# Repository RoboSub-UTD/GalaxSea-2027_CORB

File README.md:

# galaxsea 2027 corb

wassup chat... i'm playing Grand Theft Auto VI......

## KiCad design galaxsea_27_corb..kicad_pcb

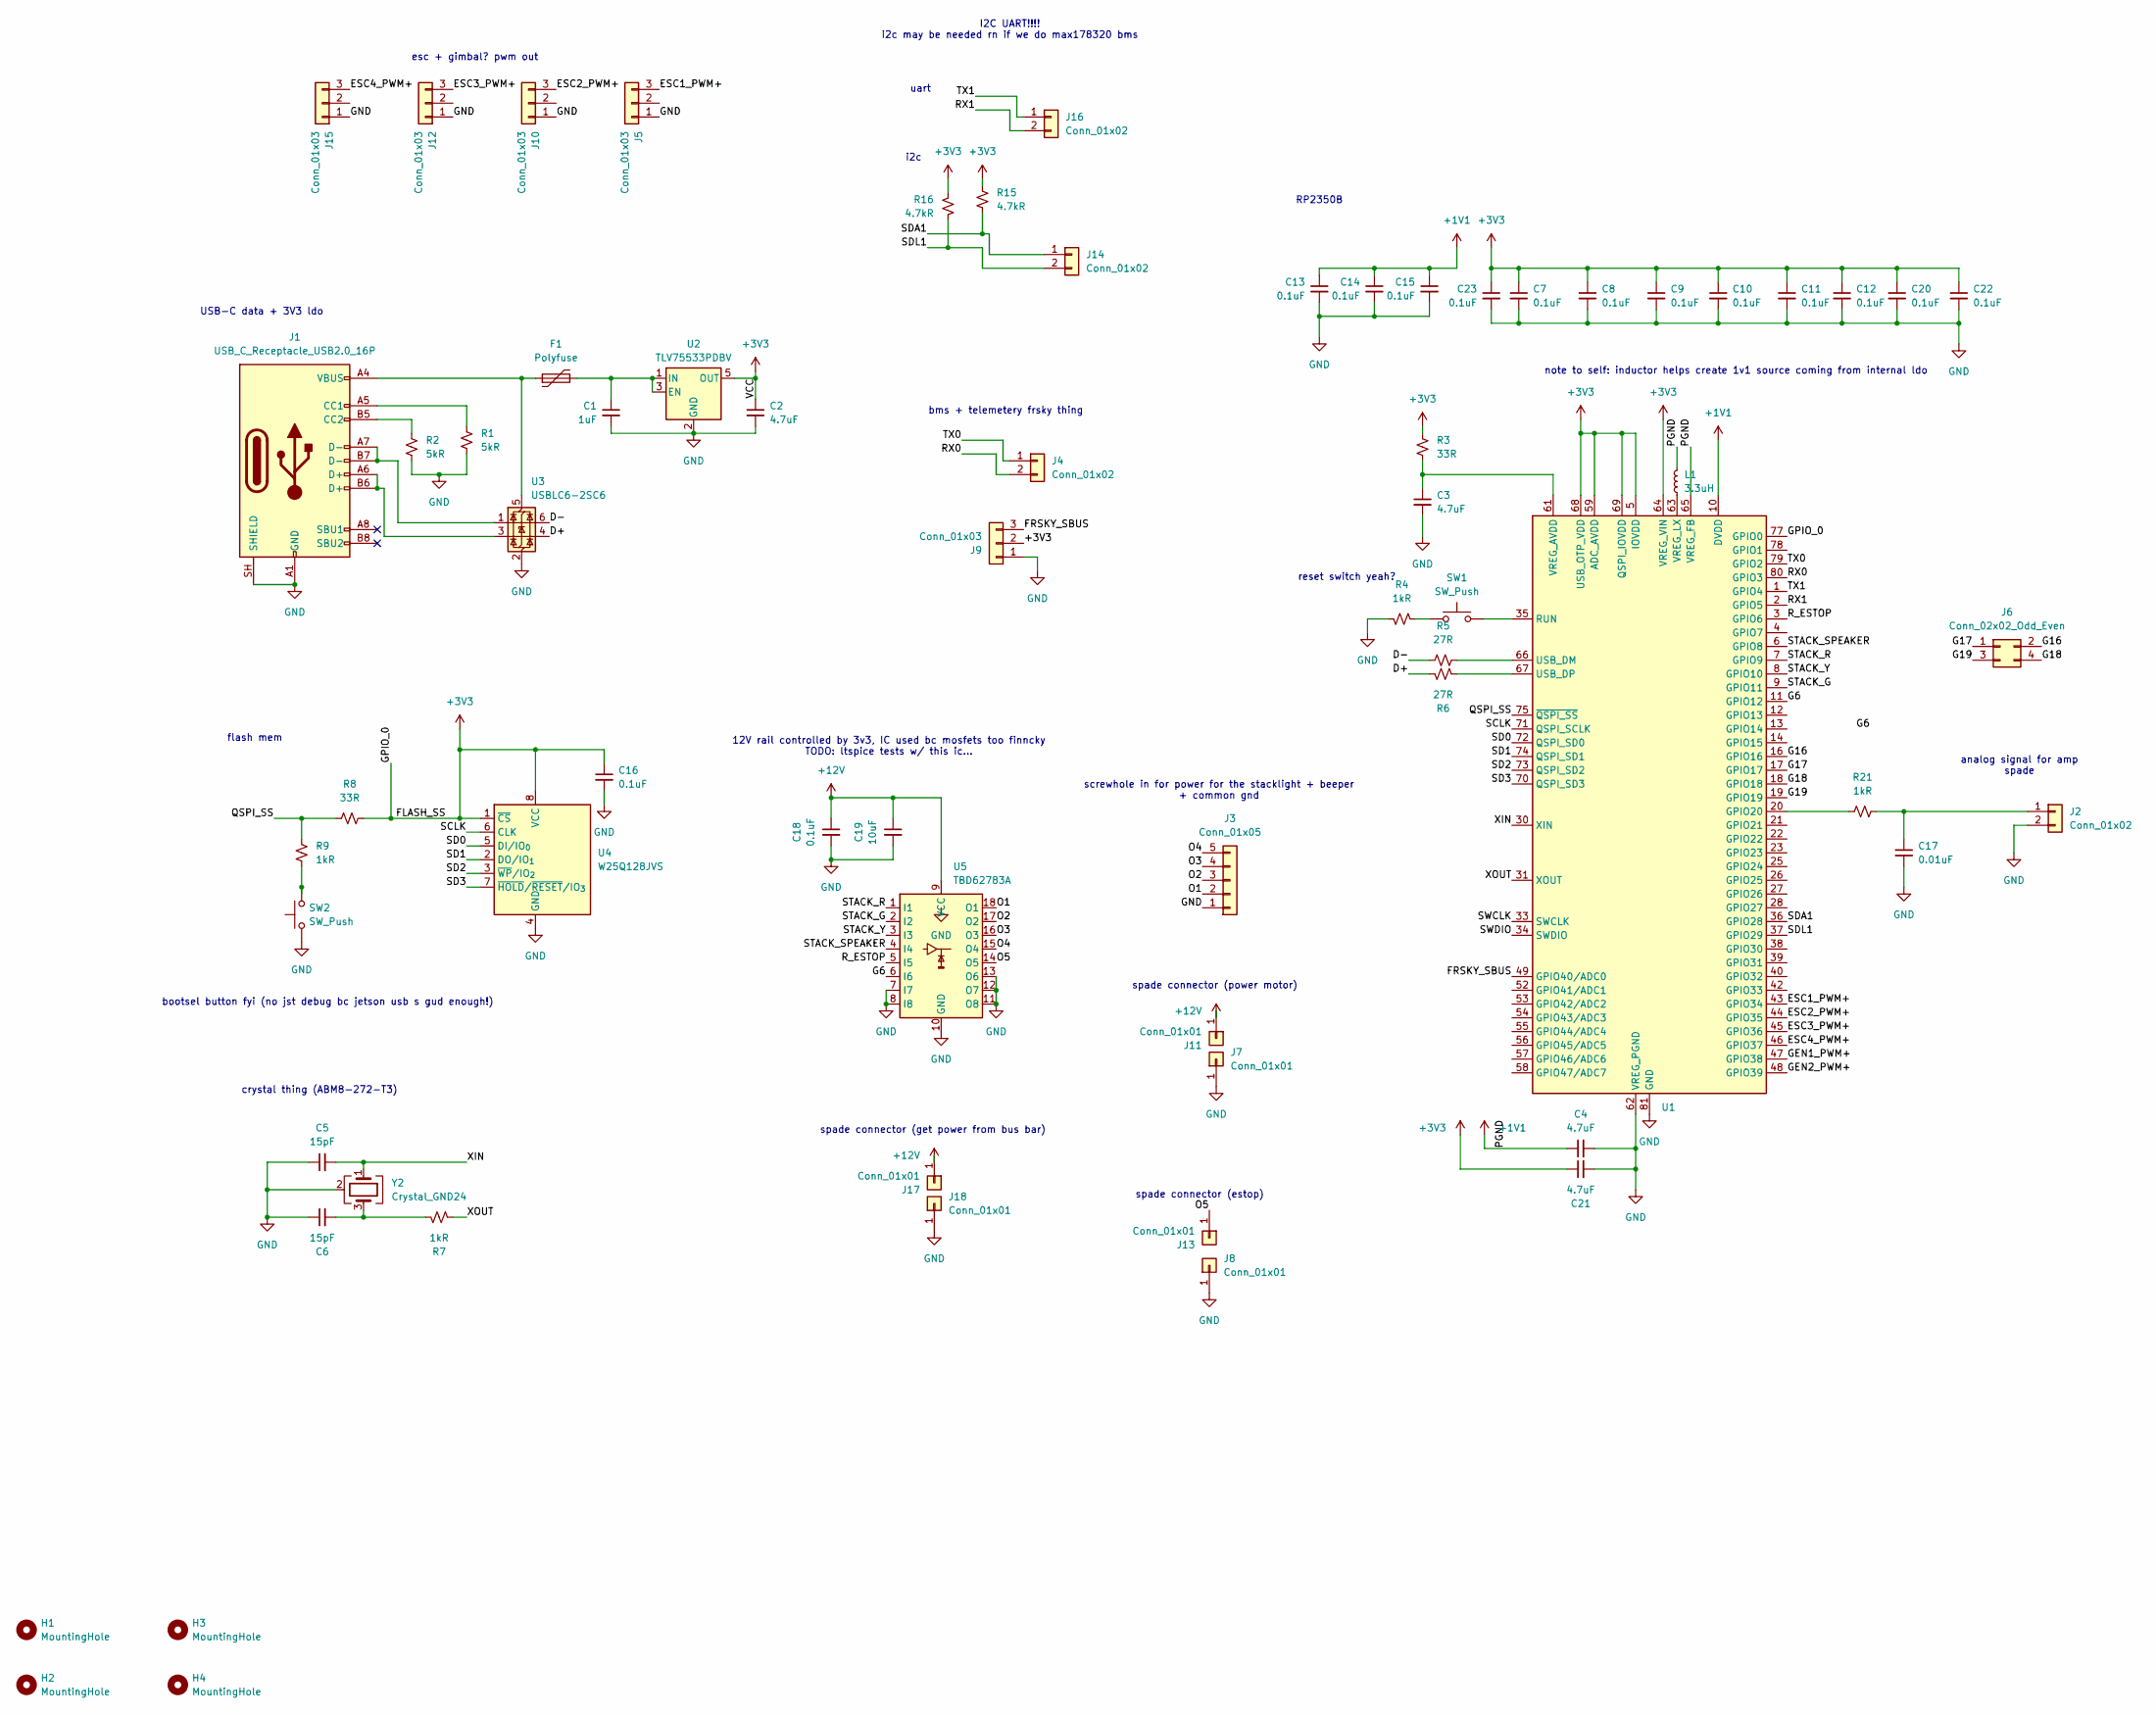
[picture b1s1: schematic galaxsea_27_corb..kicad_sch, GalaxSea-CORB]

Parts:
C1: 1uF; C_0603_1608Metric
C2, C3, C4, C21: 4.7uF; C_0603_1608Metric
C5, C6: 15pF; C_0603_1608Metric
C7, C8, C9, C10, C11, C12, C13, C14, C15, C16, C18, C20, C22, C23: 0.1uF; C_0603_1608Metric
C17: 0.01uF; C_0603_1608Metric
C19: 10uF; C_0603_1608Metric
F1: Polyfuse; Fuse_0603_1608Metric
H1, H2, H3, H4: MountingHole; MountingHole_3.2mm_M3
J1: USB_C_Receptacle_USB2.0_16P; USB_C_Receptacle_HRO_TYPE-C-31-M-12
J2, J4, J14, J16: Conn_01x02; JST_XH_B2B-XH-A_1x02_P2.50mm_Vertical
J3: Conn_01x05; TerminalBlock_RND_205-00015_1x05_P5.00mm_Horizontal
J5, J9, J10, J12, J15: Conn_01x03; JST_XH_B3B-XH-A_1x03_P2.50mm_Vertical
J6: Conn_02x02_Odd_Even; PinHeader_2x02_P2.54mm_Vertical
J7, J8, J11, J13, J17, J18: Conn_01x01; TestPoint_Bridge_Pitch5.08mm_Drill1.3mm
L1: 3.3uH; L_0603_1608Metric
R1, R2: 5kR; R_0603_1608Metric
R3, R8: 33R; R_0603_1608Metric
R4, R7, R9, R21: 1kR; R_0603_1608Metric
R5, R6: 27R; R_0603_1608Metric
R15, R16: 4.7kR; R_0603_1608Metric
SW1, SW2: SW_Push; SW_Push_1P1T_NO_Vertical_Wuerth_434133025816
U1: RP2350B; QFN-80-1EP_10x10mm_P0.4mm_EP3.4x3.4mm
U2: TLV75533PDBV; SOT-23-5
U3: USBLC6-2SC6; SOT-23-6
U4: W25Q128JVS; SOIC-8_5.3x5.3mm_P1.27mm
U5: TBD62783A; SOP-18_7x12.5mm_P1.27mm
Y2: Crystal_GND24; Crystal_SMD_3225-4Pin_3.2x2.5mm

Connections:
+1V1: C4.1, C13.1, C14.1, C15.1, L1.2, U1.10 (DVDD), U1.32 (DVDD), U1.51 (DVDD), U1.65 (VREG_FB)
+3V3: C2.1, C7.1, C8.1, C9.1, C10.1, C11.1, C12.1, C16.1, C20.1, C21.1, C22.1, C23.1, J9.2, R3.1, R8.2, R15.1, R16.1, U1.5 (IOVDD), U1.15 (IOVDD), U1.24 (IOVDD), U1.29 (IOVDD), U1.41 (IOVDD), U1.50 (IOVDD), U1.59 (ADC_AVDD), U1.60 (IOVDD), U1.64 (VREG_VIN), U1.68 (USB_OTP_VDD), U1.69 (QSPI_IOVDD), U1.76 (IOVDD), U1.77 (GPIO0), U2.5 (OUT), U4.1 (~CS), U4.8 (VCC)
+12V: C18.1, C19.1, J11.1 (Pin_1_1), J17.1 (Pin_1_1), U5.9 (VCC)
/A1: U1.52 (GPIO41/ADC1)
/A2: U1.53 (GPIO42/ADC2)
/A3: U1.54 (GPIO43/ADC3)
/A4: U1.55 (GPIO44/ADC4)
/A5: U1.56 (GPIO45/ADC5)
/A6: U1.57 (GPIO46/ADC6)
/A7: U1.58 (GPIO47/ADC7)
/D+: R6.2, U3.4 (I/O2)
/D-: R5.1, U3.6 (I/O1)
/ESC1_PWM+: J5.3, U1.43 (GPIO34)
/ESC2_PWM+: J10.3, U1.44 (GPIO35)
/ESC3_PWM+: J12.3, U1.45 (GPIO36)
/ESC4_PWM+: J15.3, U1.46 (GPIO37)
/FRSKY_SBUS: J9.3, U1.49 (GPIO40/ADC0)
/G6: U1.11 (GPIO12), U5.6 (I6)
/G16: J6.2, U1.16 (GPIO16)
/G17: J6.1, U1.17 (GPIO17)
/G18: J6.4, U1.18 (GPIO18)
/G19: J6.3, U1.19 (GPIO19)
/GEN1_PWM+: U1.47 (GPIO38)
/GEN2_PWM+: U1.48 (GPIO39)
/O1: J3.2, U5.18 (O1)
/O2: J3.3, U5.17 (O2)
/O3: J3.4, U5.16 (O3)
/O4: J3.5, U5.15 (O4)
/O5: J13.1 (Pin_1_1), U5.14 (O5)
/QSPI_SS: R8.1, R9.2, U1.75 (~QSPI_SS)
/RX0: J4.2, U1.80 (GPIO3)
/RX1: J16.2, U1.2 (GPIO5)
/R_ESTOP: U1.3 (GPIO6), U5.5 (I5)
/SCLK: U1.71 (QSPI_SCLK), U4.6 (CLK)
/SD0: U1.72 (QSPI_SD0), U4.5 (DI/IO_{0})
/SD1: U1.74 (QSPI_SD1), U4.2 (DO/IO_{1})
/SD2: U1.73 (QSPI_SD2), U4.3 (~WP/IO_{2})
/SD3: U1.70 (QSPI_SD3), U4.7 (~HOLD/~RESET/IO_{3})
/SDA1: J14.1, R15.2, U1.36 (GPIO28)
/SDL1: J14.2, R16.2, U1.37 (GPIO29)
/STACK_G: U1.9 (GPIO11), U5.2 (I2)
/STACK_R: U1.7 (GPIO9), U5.1 (I1)
/STACK_SPEAKER: U1.6 (GPIO8), U5.4 (I4)
/STACK_Y: U1.8 (GPIO10), U5.3 (I3)
/SWCLK: U1.33 (SWCLK)
/SWDIO: U1.34 (SWDIO)
/TX0: J4.1, U1.79 (GPIO2)
/TX1: J16.1, U1.1 (GPIO4)
/XIN: C5.2, U1.30 (XIN), Y2.1
/XOUT: R7.2, U1.31 (XOUT)
GND: C1.2, C2.2, C3.2, C4.2, C5.1, C6.1, C7.2, C8.2, C9.2, C10.2, C11.2, C12.2, C13.2, C14.2, C15.2, C16.2, C17.2, C18.2, C19.2, C20.2, C21.2, C22.2, C23.2, J1.A1 (GND), J1.A12 (GND), J1.B1 (GND), J1.B12 (GND), J1.SH (SHIELD), J2.2, J3.1, J5.1, J7.1 (Pin_1_1), J8.1 (Pin_1_1), J9.1, J10.1, J12.1, J15.1, J18.1 (Pin_1_1), R1.2, R2.2, R4.2, SW2.1, U1.62 (VREG_PGND), U1.81 (GND), U2.2 (GND), U3.2 (GND), U4.4 (GND), U5.7 (I7), U5.8 (I8), U5.10 (GND), U5.11 (O8), U5.12 (O7), U5.13 (O6), Y2.2 (G), Y2.4 (G)
unnamed: C6.2, R7.1, Y2.3
unnamed: J1.A5 (CC1), R1.1
unnamed: J1.B5 (CC2), R2.1
unnamed: J1.A6 (D+), J1.B6 (D+), U3.3 (I/O2)
unnamed: J1.A7 (D-), J1.B7 (D-), U3.1 (I/O1)
unnamed: C17.1, J2.1, R21.2
unnamed: R4.1, SW1.1
unnamed: R9.1, SW2.2
unnamed: R21.1, U1.20 (GPIO20)
unnamed: SW1.2, U1.35 (RUN)
unnamed: R5.2, U1.66 (USB_DM)
unnamed: R6.1, U1.67 (USB_DP)
unnamed: C3.1, R3.2, U1.61 (VREG_AVDD)
unnamed: L1.1, U1.63 (VREG_LX)
unnamed: C1.1, F1.2, U2.1 (IN), U2.3 (EN)
unnamed: F1.1, J1.A4 (VBUS), J1.A9 (VBUS), J1.B4 (VBUS), J1.B9 (VBUS), U3.5 (VBUS)

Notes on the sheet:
spade connector (power motor)
spade connector (get power from bus bar)
I2C UART!!!! i2c may be needed rn if we do max178320 bms
USB-C data + 3V3 ldo
crystal thing (ABM8-272-T3)
spade connector (estop)
bootsel button fyi (no jst debug bc jetson usb s gud enough!)
esc + gimbal? pwm out
analog signal for amp spade
uart
screwhole in for power for the stacklight + beeper + common gnd
bms + telemetery frsky thing
i2c
12V rail controlled by 3v3, IC used bc mosfets too finncky TODO: ltspice tests w/ this ic...
RP2350B
note to self: inductor helps create 1v1 source coming from internal ldo
flash mem
reset switch yeah?

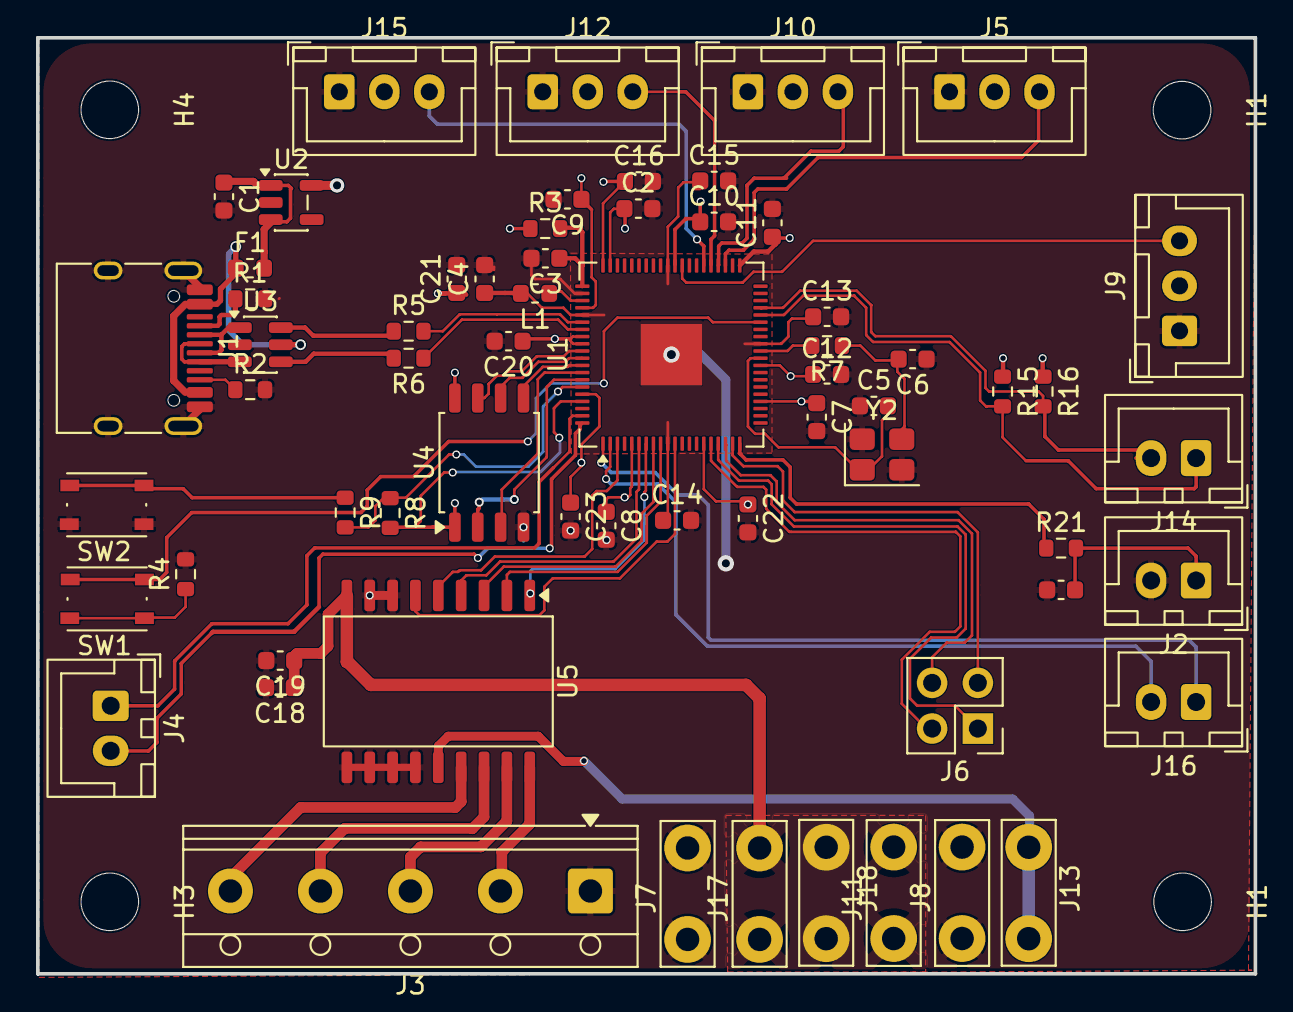
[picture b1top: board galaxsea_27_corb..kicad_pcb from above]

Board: 2 copper layers, 67.6 x 52.0 mm, 68 parts (0 on the bottom side), 56 nets.

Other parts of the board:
H1#2: MountingHole; MountingHole_3.2mm_M3
